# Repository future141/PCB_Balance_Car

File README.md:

# PCB_Balance_Car
This is the PCB design of a balanced 2 wheel car 

Use Kicad v6

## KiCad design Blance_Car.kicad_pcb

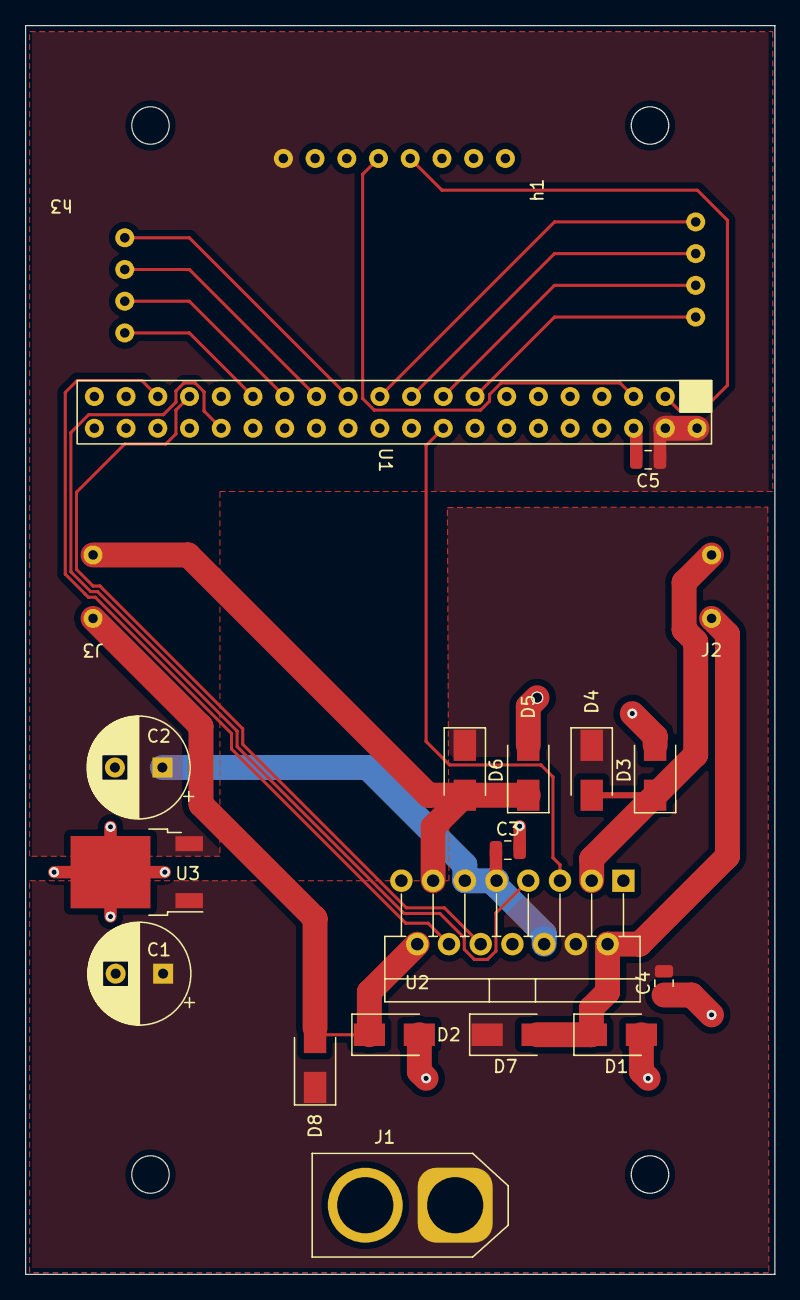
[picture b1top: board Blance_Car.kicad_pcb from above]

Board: 2 copper layers, 60.0 x 100.0 mm, 22 parts (0 on the bottom side), 21 nets.

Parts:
C1, C2: 220uf; CP_Radial_D8.0mm_P3.80mm
C3, C4, C5: 100nf; C_0805_2012Metric
D1, D2, D3, D4, D5, D6, D7, D8: SM4007; D_SMA
J1: XT60PW-M; AMASS_XT60-M_1x02_P7.20mm_Vertical
J2, J3: Conn_01x02_Female; 2_head_connector
U1: ras_head
U2: L298HN; TO-220-15_P2.54x2.54mm_StaggerOdd_Lead4.58mm_Vertical
U3: KA78M05_TO252; TO-252-2
h1: HW612; car_head
h2, h3: 4head

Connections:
+5V: C2.1, C3.1, C5.1, U1.2, U1.4, U2.6 (EnA), U2.9 (Vss), U2.11 (EnB), U3.3 (VO), h1.8
+12V: C1.1, C4.1, D2.1 (K), D4.1 (K), D6.1 (K), D8.1 (K), J1.1 (+), U2.4 (Vs), U3.1 (VI)
/GPIO12(PWM0): U1.32, U2.7 (IN2)
/GPIO13(PWM1): U1.33, U2.10 (IN3)
/GPIO18(PWM0): U1.18, U2.5 (IN1)
/GPIO19(PWM1): U1.35, U2.12 (IN4)
/Motor_sensor_1: U1.15, h2.1
/Motor_sensor_2: U1.17, h2.2
/Motor_sensor_3: U1.19, h2.3
/Motor_sensor_4: U1.21, h2.4
/Motor_sensor_5: U1.23, h3.1
/Motor_sensor_6: U1.25, h3.2
/Motor_sensor_7: U1.27, h3.3
/Motor_sensor_8: U1.29, h3.4
/SCL: U1.5, h1.5
/SDA: U1.3, h1.4
GND: C1.2, C2.2, C3.2, C4.2, C5.2, D1.2 (A), D3.2 (A), D5.2 (A), D7.2 (A), J1.2 (-), U1.6, U1.9, U1.34, U1.39, U2.1 (SENSE_A), U2.8 (GND), U2.15 (SENSE_B), U3.2 (GND), h1.6
unnamed: D1.1 (K), D2.2 (A), J2.1, U2.2 (OUT1)
unnamed: D3.1 (K), D4.2 (A), J2.2, U2.3 (OUT2)
unnamed: D5.1 (K), D6.2 (A), J3.1, U2.13 (OUT3)
unnamed: D7.1 (K), D8.2 (A), J3.2, U2.14 (OUT4)
